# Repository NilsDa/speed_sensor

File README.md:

# Speed_Sensor

This Repository contains the complete KiCad project of the speed_sensor PCB design as well as important Datasheets and lots of random files and data relating to the project.

## important directories

- **/Datasheets** -> self explanatory
- **/KiCad** -> complete KiCad project and resulting gerber files for pcb printing.
- /Software -> miscellaneous software created mainly to experiment with certain things. not critical
- rest: unsorted files and folders containing parts-lists/footprints/... (need to be properly sorted)

## possibilities for simplifying the design

- maybe ditch the rechargeable lithium battery and use a small coin battery (CR2032) instead... majorly simplifies the PCB design and reduces friction points... But, rechargeable would be nice... Just something to think about.

## LICENSE

No license because project is properly unfinished :D Whoever would want access, needs to contact me.

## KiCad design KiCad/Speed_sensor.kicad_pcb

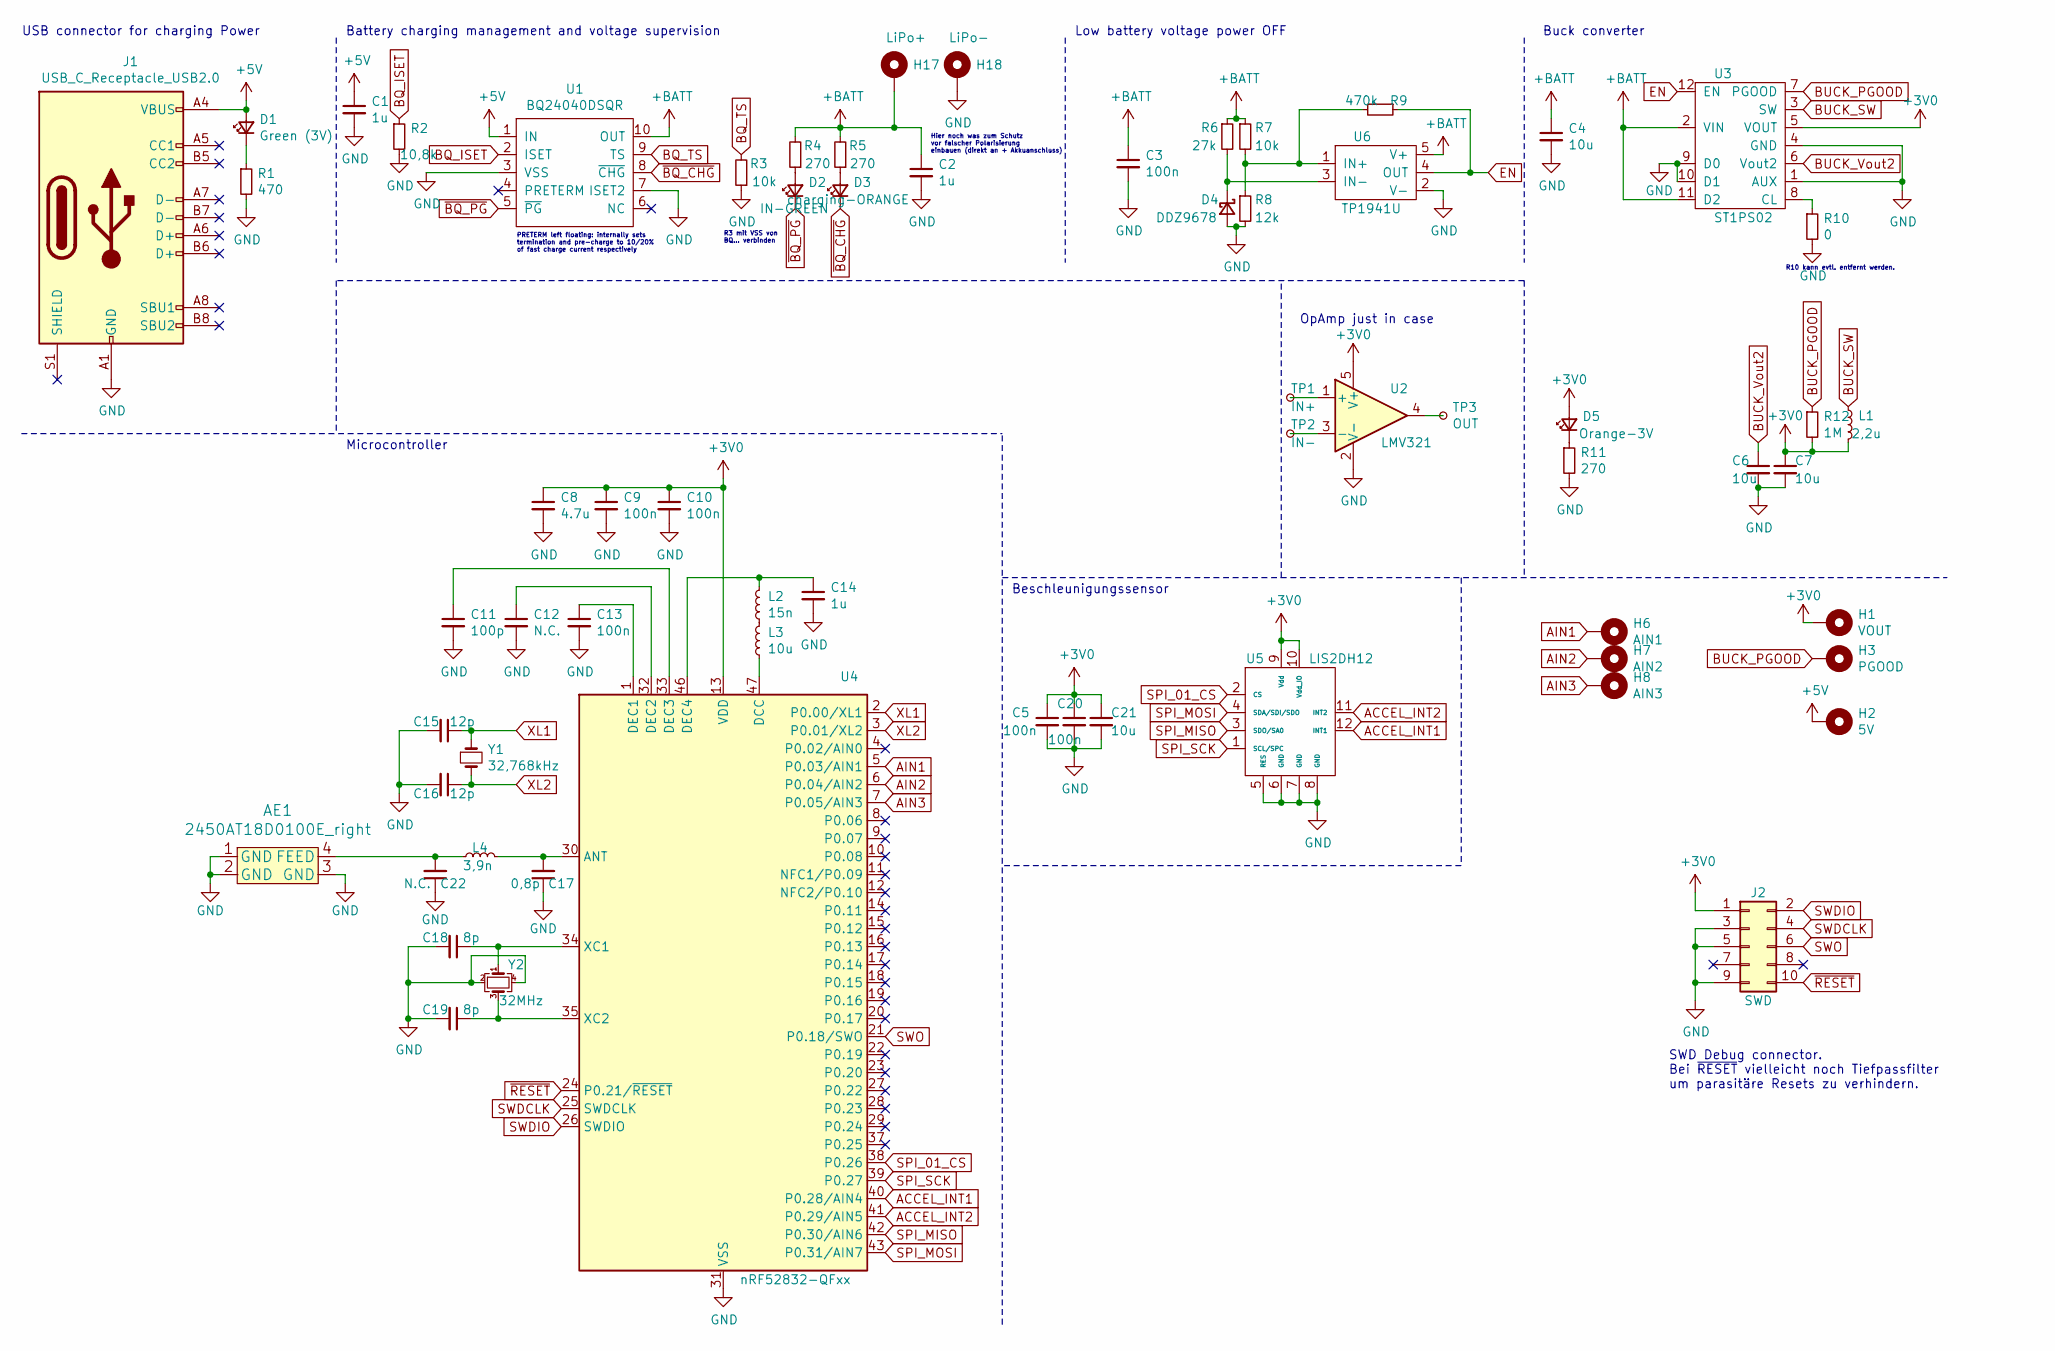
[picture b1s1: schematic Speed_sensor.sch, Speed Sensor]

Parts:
AE1: 2450AT18D0100E_right; 2450AT18D0100E
C1, C2, C14: 1u; C_0603_1608Metric_Pad1.08x0.95mm_HandSolder
C3, C5, C9, C10, C13, C20: 100n; C_0402_1005Metric_Pad0.74x0.62mm_HandSolder
C4, C6, C7, C21: 10u; C_0603_1608Metric_Pad1.08x0.95mm_HandSolder
C8: 4.7u; C_0603_1608Metric_Pad1.08x0.95mm_HandSolder
C11: 100p; C_0402_1005Metric_Pad0.74x0.62mm_HandSolder
C12, C22: N.C.; C_0402_1005Metric_Pad0.74x0.62mm_HandSolder
C15, C16: 12p; C_0402_1005Metric_Pad0.74x0.62mm_HandSolder
C17: 0,8p; C_0402_1005Metric_Pad0.74x0.62mm_HandSolder
C18, C19: 8p; C_0402_1005Metric_Pad0.74x0.62mm_HandSolder
D1: Green (3V); D_0603_1608Metric_Pad1.05x0.95mm_HandSolder
D2: IN-GREEN; D_0603_1608Metric_Pad1.05x0.95mm_HandSolder
D3: charging-ORANGE; D_0603_1608Metric_Pad1.05x0.95mm_HandSolder
D4: DDZ9678; D_SOD-123
D5: Orange-3V; D_0603_1608Metric_Pad1.05x0.95mm_HandSolder
H1: VOUT; TestPoint_Pad_D1.5mm
H2: 5V; TestPoint_Pad_D1.5mm
H3: PGOOD; TestPoint_Pad_D1.5mm
H6: AIN1; TestPoint_Pad_D1.5mm
H7: AIN2; TestPoint_Pad_D1.5mm
H8: AIN3; TestPoint_Pad_D1.5mm
H17: LiPo+; TestPoint_Plated_Hole_D2.0mm
H18: LiPo-; TestPoint_Plated_Hole_D2.0mm
J1: USB_C_Receptacle_USB2.0; USB_C_Receptacle_Palconn_UTC16-G_breitePins
J2: SWD; PinHeader_2x05_P1.27mm_Vertical_SMD
L1: 2,2u; L_0805_2012Metric_Pad1.15x1.40mm_HandSolder
L2: 15n; L_0402_1005Metric_Pad0.77x0.64mm_HandSolder
L3: 10u; L_0603_1608Metric_Pad1.05x0.95mm_HandSolder
L4: 3,9n; L_0402_1005Metric_Pad0.77x0.64mm_HandSolder
R1: 470; R_0402_1005Metric_Pad0.72x0.64mm_HandSolder
R2: 10,8k; R_0603_1608Metric_Pad0.98x0.95mm_HandSolder
R3: 10k; R_0603_1608Metric_Pad0.98x0.95mm_HandSolder
R4, R5, R11: 270; R_0402_1005Metric_Pad0.72x0.64mm_HandSolder
R6: 27k; R_0402_1005Metric_Pad0.72x0.64mm_HandSolder
R7: 10k; R_0402_1005Metric_Pad0.72x0.64mm_HandSolder
R8: 12k; R_0402_1005Metric_Pad0.72x0.64mm_HandSolder
R9: 470k; R_0402_1005Metric_Pad0.72x0.64mm_HandSolder
R10: 0; R_0402_1005Metric_Pad0.72x0.64mm_HandSolder
R12: 1M; R_0402_1005Metric_Pad0.72x0.64mm_HandSolder
TP1: IN+; TestPoint_Pad_D1.5mm
TP2: IN-; TestPoint_Pad_D1.5mm
TP3: OUT; TestPoint_Pad_D1.5mm
U1: BQ24040DSQR; BQ24040DSQR_breitePins
U2: LMV321; SOT-23-5_HandSoldering
U3: ST1PS02; ST1PS02CQTR_breitePins
U4: nRF52832-QFxx; QFN-48-1EP_6x6mm_P0.4mm_EP4.6x4.6mm_Handsolder
U5: LIS2DH12; LGA-12_2x2mm_P0.5mm_Handsolder
U6: TP1941U; SOT-353_SC-70-5_Handsoldering
Y1: 32,768kHz; Crystal_SMD_G8-2Pin_3.2x1.5mm
Y2: 32MHz; SMD-2016_4P

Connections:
+3V0: C5.1, C7.1, C8.1, C9.1, C10.1, C20.1, C21.1, D5.2 (A), H1.1, J2.1, L1.2, R12.2, U2.5 (V+), U3.5 (VOUT), U4.13 (VDD), U4.36 (VDD), U4.48 (VDD), U5.9 (Vdd), U5.10 (Vdd_IO)
+5V: C1.1, D1.2 (A), H2.1, J1.A4 (VBUS), J1.A9 (VBUS), J1.B4 (VBUS), J1.B9 (VBUS), U1.1 (IN); also elsewhere on the board
+BATT: C2.1, C3.1, C4.1, H17.1, R4.2, R5.2, R6.1, R7.1, U1.10 (OUT), U3.2 (VIN), U3.11 (D2), U6.5 (V+)
ACCEL_INT1: U4.40 (P0.28/AIN4), U5.12 (INT1)
ACCEL_INT2: U4.41 (P0.29/AIN5), U5.11 (INT2)
AIN1: H6.1, U4.5 (P0.03/AIN1)
AIN2: H7.1, U4.6 (P0.04/AIN2)
AIN3: H8.1, U4.7 (P0.05/AIN3)
BQ_ISET: R2.1, U1.2 (ISET)
BQ_TS: R3.2, U1.9 (TS)
BUCK_PGOOD: H3.1, R12.1, U3.7 (PGOOD)
BUCK_SW: L1.1, U3.3 (SW)
BUCK_Vout2: C6.1, U3.6 (Vout2)
EN: R9.1, U3.12 (EN), U6.4 (OUT)
GND: AE1.1 (GND), AE1.2 (GND), AE1.3 (GND), C1.2, C2.2, C3.2, C4.2, C5.2, C6.2, C7.2, C8.2, C9.2, C10.2, C11.2, C12.2, C13.2, C14.2, C15.2, C16.2, C17.1, C18.2, C19.2, C20.2, C21.2, C22.1, D4.2 (A), H18.1, J1.A1 (GND), J1.A12 (GND), J1.B1 (GND), J1.B12 (GND), J2.3, J2.5, J2.9, R1.2, R2.2, R3.1, R8.2, R10.2, R11.2, U1.3 (VSS), U1.7 (ISET2), U2.2 (V-), U3.1 (AUX), U3.4 (GND), U3.9 (D0), U3.10 (D1), U4.31 (VSS), U4.45 (VSS), U4.49 (VSS), U5.5 (RES), U5.6 (GND), U5.7 (GND), U5.8 (GND), U6.2 (V-), Y2.2, Y2.4
unnamed: AE1.4 (FEED), C22.2, L4.1
unnamed: C11.1, U4.33 (DEC3)
unnamed: C12.1, U4.32 (DEC2)
unnamed: C13.1, U4.1 (DEC1)
unnamed: C14.1, L2.2, U4.46 (DEC4)
unnamed: C17.2, L4.2, U4.30 (ANT)
unnamed: C18.1, U4.34 (XC1), Y2.1
unnamed: C19.1, U4.35 (XC2), Y2.3
unnamed: D1.1 (K), R1.1
unnamed: D2.2 (A), R4.1
unnamed: D3.2 (A), R5.1
unnamed: D4.1 (K), R6.2, U6.3 (IN-)
unnamed: D5.1 (K), R11.1
unnamed: L2.1, L3.2
unnamed: L3.1, U4.47 (DCC)
unnamed: R7.2, R8.1, R9.2, U6.1 (IN+)
unnamed: R10.1, U3.8 (CL)
unnamed: TP1.1, U2.1 (+)
unnamed: TP2.1, U2.3 (-)
unnamed: TP3.1, U2.4
SPI_01_CS: U4.38 (P0.26), U5.2 (CS)
SPI_MISO: U4.42 (P0.30/AIN6), U5.3 (SDO/SA0)
SPI_MOSI: U4.43 (P0.31/AIN7), U5.4 (SDA/SDI/SDO)
SPI_SCK: U4.39 (P0.27), U5.1 (SCL/SPC)
SWDCLK: J2.4, U4.25 (SWDCLK)
SWDIO: J2.2, U4.26 (SWDIO)
SWO: J2.6, U4.21 (P0.18/SWO)
XL1: C15.1, U4.2 (P0.00/XL1), Y1.1
XL2: C16.1, U4.3 (P0.01/XL2), Y1.2
~BQ_CHG~: D3.1 (K), U1.8 (~CHG~)
~BQ_PG~: D2.1 (K), U1.5 (~PG~)
~RESET~: J2.10, U4.24 (P0.21/~RESET)

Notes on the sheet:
Microcontroller
Beschleunigungssensor
SWD Debug connector. Bei ~RESET~ vielleicht noch Tiefpassfilter um parasitäre Resets zu verhindern.
USB connector for charging Power
Battery charging management and voltage supervision
Hier noch was zum Schutz vor falscher Polarisierung einbauen (direkt an + Akkuanschluss)
Low battery voltage power OFF
Buck converter
PRETERM left floating: internally sets termination and pre-charge to 10/20% of fast charge current respectively
R10 kann evtl. entfernt werden.
R3 mit VSS von BQ... verbinden
OpAmp just in case

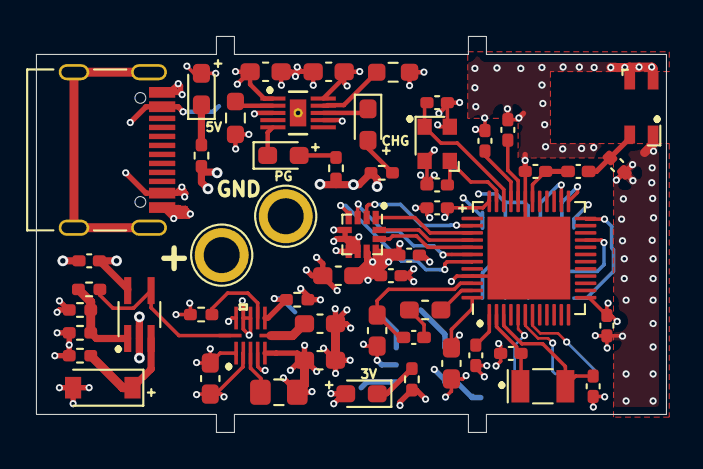
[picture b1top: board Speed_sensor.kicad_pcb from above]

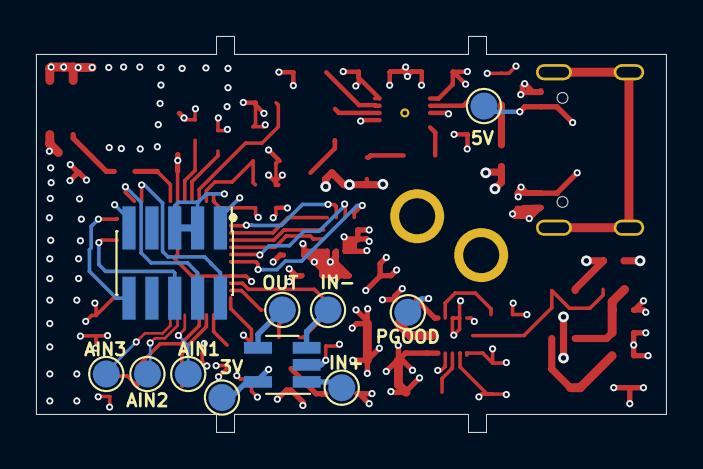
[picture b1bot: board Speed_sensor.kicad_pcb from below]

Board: 4 copper layers, 35.0 x 22.0 mm, 65 parts (11 on the bottom side), 47 nets.

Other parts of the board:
5V: 5V; TestPoint_Pad_D1.5mm

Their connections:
+5V: 5V.1; also elsewhere on the board

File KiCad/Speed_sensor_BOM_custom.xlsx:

Source: | C:\Users\nils_\OneDrive\Documents\Projekte\Speed_sensor\speed_sensor\KiCad\Spee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
Date: | 44328.924131944441
Tool: | Eeschema (5.1.9)-1
Component Count: | 61
Ref | Value | Footprint | Bestückung | Datasheet | Comment | LCSC part no. | hat Manu
AE1 | 2450AT18D0100E_right | myparts:2450AT18D0100E |  | ~ |  |  | ja
C1 | 1u | Capacitor_SMD:C_0603_1608Metric_Pad1.08x0.95mm_HandSolder | 16 | ~ |  | C1592 | nein
C2 | 1u | Capacitor_SMD:C_0603_1608Metric_Pad1.08x0.95mm_HandSolder | 16 | ~ |  | C1592 | nein
C3 | 100n | Capacitor_SMD:C_0402_1005Metric_Pad0.74x0.62mm_HandSolder | 2 | ~ |  | C392963 | ja, aber trotzdem bestellen
C4 | 10u | Capacitor_SMD:C_0603_1608Metric_Pad1.08x0.95mm_HandSolder | 17 | ~ |  | C319196 | nein
C5 | 100n | Capacitor_SMD:C_0402_1005Metric_Pad0.74x0.62mm_HandSolder | 2 | ~ |  | C392963 | ja, aber trotzdem bestellen
C6 | 10u | Capacitor_SMD:C_0603_1608Metric_Pad1.08x0.95mm_HandSolder | 17 | ~ |  | C319196 | nein
C7 | 10u | Capacitor_SMD:C_0603_1608Metric_Pad1.08x0.95mm_HandSolder | 17 | ~ |  | C319196 | nein
C8 | 4.7u | Capacitor_SMD:C_0603_1608Metric_Pad1.08x0.95mm_HandSolder | 18 | ~ |  | C19666 | nein
C9 | 100n | Capacitor_SMD:C_0402_1005Metric_Pad0.74x0.62mm_HandSolder | 2 | ~ |  | C392963 | ja, aber trotzdem bestellen
C10 | 100n | Capacitor_SMD:C_0402_1005Metric_Pad0.74x0.62mm_HandSolder | 2 | ~ |  | C392963 | ja, aber trotzdem bestellen
C11 | 100p | Capacitor_SMD:C_0402_1005Metric_Pad0.74x0.62mm_HandSolder | 3 | ~ |  | C696853 | ja
C12 | N.C. | Capacitor_SMD:C_0402_1005Metric_Pad0.74x0.62mm_HandSolder |  | ~ |  |  | -
C13 | 100n | Capacitor_SMD:C_0402_1005Metric_Pad0.74x0.62mm_HandSolder | 2 | ~ |  | C392963 | ja, aber trotzdem bestellen
C14 | 1u | Capacitor_SMD:C_0603_1608Metric_Pad1.08x0.95mm_HandSolder | 16 | ~ |  | C1592 | nein
C15 | 12p | Capacitor_SMD:C_0402_1005Metric_Pad0.74x0.62mm_HandSolder | 1 | ~ |  | C26406 | nein
C16 | 12p | Capacitor_SMD:C_0402_1005Metric_Pad0.74x0.62mm_HandSolder | 1 | ~ |  | C26406 | nein
C17 | 0,8p | Capacitor_SMD:C_0402_1005Metric_Pad0.74x0.62mm_HandSolder | 4 | ~ |  | C40459 | ja
C18 | 8p | Capacitor_SMD:C_0402_1005Metric_Pad0.74x0.62mm_HandSolder | 5 | ~ |  | C258500 | nein
C19 | 8p | Capacitor_SMD:C_0402_1005Metric_Pad0.74x0.62mm_HandSolder | 5 | ~ |  | C258500 | nein
C20 | 100n | Capacitor_SMD:C_0402_1005Metric_Pad0.74x0.62mm_HandSolder | 2 | ~ |  | C392963 | ja, aber trotzdem bestellen
C21 | 10u | Capacitor_SMD:C_0603_1608Metric_Pad1.08x0.95mm_HandSolder | 17 | ~ |  | C319196 | nein
C22 | N.C. | Capacitor_SMD:C_0402_1005Metric_Pad0.74x0.62mm_HandSolder |  | ~ |  |  | -
D1 | Green (3V) | Diode_SMD:D_0603_1608Metric_Pad1.05x0.95mm_HandSolder |  | ~ |  | C205443 | ja
D2 | IN-GREEN | Diode_SMD:D_0603_1608Metric_Pad1.05x0.95mm_HandSolder |  | ~ |  | C205443 | ja
D3 | charging-ORANGE | Diode_SMD:D_0603_1608Metric_Pad1.05x0.95mm_HandSolder |  | ~ |  | C205445 | ja
D4 | DDZ9678 | Diode_SMD:D_SOD-123 |  | ~ |  | C150464 | ja
D5 | Orange-3V | Diode_SMD:D_0603_1608Metric_Pad1.05x0.95mm_HandSolder |  | ~ |  | C205445 | ja
H1 | VOUT | TestPoint:TestPoint_Pad_D1.5mm |  | ~ |  |  | -
H3 | PGOOD | TestPoint:TestPoint_Pad_D1.5mm |  | ~ |  |  | -
H6 | AIN1 | TestPoint:TestPoint_Pad_D1.5mm |  | ~ |  |  | -
H7 | AIN2 | TestPoint:TestPoint_Pad_D1.5mm |  | ~ |  |  | -
H8 | AIN3 | TestPoint:TestPoint_Pad_D1.5mm |  | ~ |  |  | -
H17 | LiPo+ | TestPoint:TestPoint_Plated_Hole_D2.0mm |  | ~ |  |  | -
H18 | LiPo- | TestPoint:TestPoint_Plated_Hole_D2.0mm |  | ~ |  |  | -
J1 | USB_C_Receptacle_USB2.0 | myparts:USB_C_Receptacle_Palconn_UTC16-G_breitePins |  | https://www.usb.org/sites/default/files/documents/usb_type-c.zip |  | C165948 | nein
J2 | SWD | Connector_PinHeader_1.27mm:PinHeader_2x05_P1.27mm_Vertical_SMD |  | ~
L1 | 2,2u | Inductor_SMD:L_0805_2012Metric_Pad1.15x1.40mm_HandSolder | 22 | ~ |  | C95973 | nein
L2 | 15n | Inductor_SMD:L_0402_1005Metric_Pad0.77x0.64mm_HandSolder | 6 | ~ |  | C329619 | nein
L3 | 10u | Inductor_SMD:L_0603_1608Metric_Pad1.05x0.95mm_HandSolder | 19 | ~ |  | C1035 | nein
L4 | 3,9n | Inductor_SMD:L_0402_1005Metric_Pad0.77x0.64mm_HandSolder | 7 | ~ |  | C90196 | ja
R1 | 470 | Resistor_SMD:R_0402_1005Metric_Pad0.72x0.64mm_HandSolder | 8 | ~ | verwende 510 | C25170 | ja
R2 | 10,8k | Resistor_SMD:R_0603_1608Metric_Pad0.98x0.95mm_HandSolder | 20 | ~ | verwende 10,7k | C22857 | nein
R3 | 10k | Resistor_SMD:R_0603_1608Metric_Pad0.98x0.95mm_HandSolder | 21 | ~ |  | C305012 | ja (nur 20)
R4 | 270 | Resistor_SMD:R_0402_1005Metric_Pad0.72x0.64mm_HandSolder | 9 | ~ |  | C310256 | ja
R5 | 270 | Resistor_SMD:R_0402_1005Metric_Pad0.72x0.64mm_HandSolder | 9 | ~ |  | C310256 | ja
R6 | 27k | Resistor_SMD:R_0402_1005Metric_Pad0.72x0.64mm_HandSolder | 10 | ~ |  | C304599 | ja
R7 | 10k | Resistor_SMD:R_0402_1005Metric_Pad0.72x0.64mm_HandSolder | 11 | ~ |  | C140214 | ja
R8 | 12k | Resistor_SMD:R_0402_1005Metric_Pad0.72x0.64mm_HandSolder | 12 | ~ |  | C25535 | ja
R9 | 470k | Resistor_SMD:R_0402_1005Metric_Pad0.72x0.64mm_HandSolder | 13 | ~ |  | C294637 | ja
R10 | 0 | Resistor_SMD:R_0402_1005Metric_Pad0.72x0.64mm_HandSolder | 14 | ~ |  | C60485 | ja
R11 | 270 | Resistor_SMD:R_0402_1005Metric_Pad0.72x0.64mm_HandSolder | 9 | ~ |  | C310256 | ja
R12 | 1M | Resistor_SMD:R_0402_1005Metric_Pad0.72x0.64mm_HandSolder | 15 | ~ |  | C26087 | ja
U1 | BQ24040DSQR | Package_WSON-10:BQ24040DSQR_breitePins |  |  |  | C81080 | ja
U2 | LMV321 | Package_TO_SOT_SMD:SOT-23-5_HandSoldering |  | http://www.ti.com/lit/ds/symlink/lmv324.pdf |  |  | ja
U3 | ST1PS02 | Package_TQFN-12:ST1PS02CQTR_breitePins |  |  | Free Sample (5x) |  | nein
U4 | nRF52832-QFxx | myparts:QFN-48-1EP_6x6mm_P0.4mm_EP4.6x4.6mm_Handsolder |  | http://infocenter.nordicsemi.com/pdf/nRF52832_PS_v1.4.pdf |  |  | ja
U5 | LIS2DH12 | myparts:LGA-12_2x2mm_P0.5mm_Handsolder |  |  |  | C110926 | ja
U6 | TP1941U | Package_TO_SOT_SMD:SOT-353_SC-70-5_Handsoldering |  |  |  | C248711 | ja
Y1 | 32,768kHz | Crystal:Crystal_SMD_G8-2Pin_3.2x1.5mm |  | ~ |  |  | ja
Y2 | 32MHz | myparts:SMD-2016_4P |  | ~ |  |  | ja

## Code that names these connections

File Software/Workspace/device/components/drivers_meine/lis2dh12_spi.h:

/*

Driver for lis2dh12 connected via SPI

Autor: Nils Daub

this driver is specific to the 
*/

#ifndef LIS2DH12_SPI_H
#define LIS2DH12_SPI_H

#ifdef __cplusplus
extern "C" {
#endif

// includes
// #include "lis2dh12_internal.h"
#include "nrf_drv_spi.h"
#include "nrf_gpio.h"


/**
 * @brief Possible sensor addresses.
 */
#define LIS2DH12_BASE_ADDRESS_LOW       0x18U
#define LIS2DH12_BASE_ADDRESS_HIGH      0x19U

// WHO_AM_I default value.
#define LIS2DH12_REG_WHO_AM_I_DEFAULT_VALUE 0x33

// lis2dh12 registers
#define LIS2DH12_REG_STATUS_AUX         0x07
#define LIS2DH12_REG_OUT_TEMP_L         0x0C
#define LIS2DH12_REG_OUT_TEMP_H         0x0D
#define LIS2DH12_REG_WHO_AM_I           0x0F
#define LIS2DH12_REG_CTRL_REG0          0x1E
#define LIS2DH12_REG_TEMP_CFG_REG       0x1F
#define LIS2DH12_REG_CTRL_REG1          0x20
#define LIS2DH12_REG_CTRL_REG2          0x21
#define LIS2DH12_REG_CTRL_REG3          0x22
#define LIS2DH12_REG_CTRL_REG4          0x23
#define LIS2DH12_REG_CTRL_REG5          0x24
#define LIS2DH12_REG_CTRL_REG6          0x25
#define LIS2DH12_REG_REFERENCE          0x26
#define LIS2DH12_REG_STATUS             0x27
#define LIS2DH12_REG_OUT_X_L            0x28
#define LIS2DH12_REG_OUT_X_H            0x29
#define LIS2DH12_REG_OUT_Y_L            0x2A
#define LIS2DH12_REG_OUT_Y_H            0x2B
#define LIS2DH12_REG_OUT_Z_L            0x2C
#define LIS2DH12_REG_OUT_Z_H            0x2D
#define LIS2DH12_REG_FIFO_CTRL          0x2E
#define LIS2DH12_REG_FIFO_SRC           0x2F
#define LIS2DH12_REG_INT1_CFG           0x30
#define LIS2DH12_REG_INT1_SRC           0x31
#define LIS2DH12_REG_INT1_THS           0x32
#define LIS2DH12_REG_INT1_DURATION      0x33
#define LIS2DH12_REG_INT2_CFG           0x34
#define LIS2DH12_REG_INT2_SRC           0x35
#define LIS2DH12_REG_INT2_THS           0x36
#define LIS2DH12_REG_INT2_DURATION      0x37
#define LIS2DH12_REG_CLICK_CFG          0x38
#define LIS2DH12_REG_CLICK_SRC          0x39
#define LIS2DH12_REG_CLICK_THS          0x3A
#define LIS2DH12_REG_TIME_LIMIT         0x3B
#define LIS2DH12_REG_TIME_LATENCY       0x3C
#define LIS2DH12_REG_TIME_WINDOW        0x3D
#define LIS2DH12_REG_ACT_THS            0x3E
#define LIS2DH12_REG_ACT_DUR            0x3F


// SPI buffer
#define SPI_BUFSIZE 8   // 8 byte SPI buffer size
static uint8_t spi_tx_buf[SPI_BUFSIZE];    // transfer buffer
static uint8_t spi_rx_buf[SPI_BUFSIZE];    // receive buffer


// set read or write operation
#define SET_READ_SINGLE_CMD(x) (x | 0x80)   // set MSB to 1 for read operation



static volatile bool spi_xfer_done;     // transmission completion flag



/*
Event Handler
setting flag spi_xfer_done (to indicate communication has completed)
*/
void spi_event_handler(nrf_drv_spi_evt_t const * p_event, void * p_context);


/*
init function for spi connection to this sensor
input: spi instance
*/
//void LIS2DH12_spi_init(nrf_drv_spi_t const * const spi_instance, int LIS2DH12_SS_PIN, int SPI_MISO_PIN, int SPI_MOSI_PIN, int SPI_SCK_PIN);
void LIS2DH12_spi_init(nrf_drv_spi_t const * const spi_instance, nrf_drv_spi_config_t spi_config);


/*
function to read specified Register
*/
int LIS2DH12_read_reg(nrf_drv_spi_t const * const spi_instance, int reg);

/*
function to write a Byte into specified register
*/
void LIS2DH12_write_reg(nrf_drv_spi_t const * const spi_instance, int reg, int write_reg);

/*
function to enable Power-down mode (current consumption 0,5uA)
*/
void LIS2DH12_power_down_mode(nrf_drv_spi_t const * const spi_instance);

/*
function to disable power-down/enable low-power mode (25Hz; 6uA)
*/
void LIS2DH12_low_power_mode(nrf_drv_spi_t const * const spi_instance);


#ifdef __cplusplus
}
#endif

#endif // LIS2DH12_SPI_H

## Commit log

2021-04-26 some datasheets
2021-04-26 all initial KiCad files (only schematics started)
2021-04-26 added cd of this folder to not waste time
2021-04-26 hierarchische Aufteilung der Schematic angefangen & power circuit um Battery management + usb connector erweitert
2021-04-26 Schematic ein bisschen sortiert
2021-04-26 added green LED for when USB is connected to power circuit
2021-04-26 changed SPI labels to make it more general and not specific to the BMA Sensor
2021-04-26 added battery voltage supervision version 1
2021-04-26 added files for reference design for cc2570
2021-04-27 corrected battery voltage supervision
2021-04-27 paar Kommentare/Ideen zur voltage supervision hinzugefügt
2021-04-27 int pins am BMA hinzugefügt (aber noch nicht an nrf angeschlossen
2021-04-27 ANT bauteile vom nrf entfernt
2021-04-27 Kommentar zum ANT Modul
2021-04-27 kleines Kommentar angepasst
2021-04-27 paar Sachen mit Manu angepasst
2021-04-27 power circuit übersichtlicher gemacht, low battery voltage detection verändert.
2021-04-28 updated battery charging with Manus chip, added low frequency crystal
2021-04-28 switch to Manus Accelerometer, switch back to A4 page size
2021-04-28 buck converter circuit made more readable
2021-04-28 antenna added
2021-04-28 added pads for all AINx, decided on which GPIO to use (wil prop change again)
2021-04-28 added small comment)
2021-04-28 added all annotations
2021-04-28 added a lot of footprints (mainly crystal and all the chips are missing)
2021-04-30 added all footprints (LFO crystal might have to be updated)
2021-04-30 custom footprints von Manu übernommen (jetzt sollte alles passen), PCB layout angefangen.
2021-04-30 layout update (Bauteile um den nrf grob positioniert)
2021-04-30 parts of power circuit roughly layouted
2021-04-30 parts of power circuit roughly layouted, again
2021-04-30 layout. parts roughly put into the right spot
2021-05-01 played around with part positioning slightly
2021-05-01 small changes in the layout
2021-05-02 layout part placement (again, very small changes)
2021-05-02 changed some labels in the .sch so all power stuff is labeled correctly
2021-05-02 changed which GPIO pins are used for SPI
2021-05-04 layout part positions changed slightly, added 3,5cm x 2cm outline (as a goal)
2021-05-04 defined PCB size 35mm x 20mm, started rearranging layout (starting with power circuit (5V + Batt low voltage turn OFF)
2021-05-04 added Buck converter part to the properly sized layout
2021-05-04 Bauteilbezeichnungen auf nicht mehr sichtbar gemacht
2021-05-04 Layout um den nrf an Referenzlayout orientiert.
2021-05-04 kompletter power circuit kompakt im layout untergebracht.
2021-05-04 Bauteilplatzierungen leicht angepasst. Bemerkt, dass PCB wahrsch größer werden muss.
2021-05-05 kleine Änderungen an Bauteilplatzierungen um vias unterbringen zu können, 'keepout area' für Antenne eingefügt.
2021-05-05 Änderungen nach Treffen mit Manu, opamp für alle Fälle, opamp footprint geändert, C footprint in impedance matching circuit hinzugefügt, SWD connector footprint geändert.
2021-05-05 upgrade auf USB-C connector & footprint
2021-05-05 buck converter footprint pads verkleinert, nrf + naheliegende bauteile gedreht eingefügt, Antenne neu platziert
2021-05-08 Datasheet für quarz hinzugefügt, kleine änderungen am Layout (nichts nennenswertes)
2021-05-10 power und GND plane aufgeteilt (quarze noch nicht beachtet, Antenne aber schon)
2021-05-10 angefangen mit dem routing
2021-05-10 erste Layout-version fast fertig geroutet
2021-05-10 nochmal bisschen am Layout
2021-05-10 Änderungen am layout: vias, leitungen & pads leicht umplatziert
2021-05-10 kleine layout-änderungen, mal wieder
2021-05-12 angefangen die genauen Bauteile zuzuordnen, paar footprints geändert (LED-widerstände von 0603 zu 0402)
2021-05-12 weitere Bauteile zugeordnet (Widerstände und Dioden)
2021-05-15 unbedeutende kleine Änderungen am Layout.
2021-05-19 updated footprint L1, BOM erweitert und weitere Teile zugeordnet
2021-05-20 im layout paar Bezeichnungen entfernt (die zurück gekommen sind nachdem footprints geändert wurden)
2021-05-21 erste Beschriftungen ins Layout eingefügt (sehr wenig, rückseite kann noch nichts eingefügt werden...)
2021-05-22 paar Markierungen für + Voltage sowie PIN1 im layout hinzugefügt
2021-05-29 restliche Bauteile zugeornet und raus gesucht (bei LCSC bereit zum Bestellen); restliche Markierungen im Layout gemacht; 4 Kerben an langen Seiten des PCB hinzugefügt um ggf. PCB in Gehäuse zu drücke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
2021-05-29 erste Bestellung bei LCSC gemacht (siehe excel-tabelle)
2021-05-29 design rule check im layout durchgeführt und kleinigkeiten angepasst
2021-05-29 alle Files zum Bestellen erstellt und Bestellungen bei jlcpcb und lcsc raus geschickt :).
2021-05-31 segger embeded Studio installiert und erstes Projekt erstellt.
2021-06-05 unnötige Dateien entfernt.
2021-06-05 visual studio code Workspace angelegt und relevante Teile des SDK eingefügt. erste CMakeLists erstellt und erste anpassungen gemacht.
2021-06-07 .gitignore hinzugefügt und SDK sowie ein paar andere Sachen hinzugefügt; SDK nochmal mit allen Ordnern (außer examples) hinzugefügt.
2021-06-07 build ordner zu .gitignore hinzugefügt.
2021-06-07 .xlsx der bestellung umbenannt (Monat berichtigt).
2021-06-07 source files in CMakeLists angepasst.
2021-06-07 linker file hinzugefügt
2021-06-09 paar Änderungen an der CMakeLists.txt von gestern; Excel der Bestellung vom 01.Juni angepasst (alles angekommen :)))
2021-06-18 CMakeLists.txt leicht angepasst
2021-07-19 BOM tabelle nach erster Bestückung
2021-07-21 some changes to CMakeLists; added some Matlab Test stuff
2021-07-21 connected BQ2404... Thermal Pad to GND
2021-07-21 added 5V Test Pad on backside
2021-07-21 added back-SilkS and all Pad-Names + Pin1 marking at SWD footprintgit status
2021-08-10 einfach GPIO Pin5 (AIN3) toggle Beispiel
2021-08-10 .../device/ Directory aus .gitignore entfernt
2021-08-10 .../device/ Directory hinzugefügt. (die ganze SDK eben)
2021-09-19 VScode zum funktionieren gebracht und LIS2DH12 driver angefangen
2021-09-20 submodule für Firmware hinzugefügt.
2021-09-20 kleine submodule tests
2021-09-20 get new submodule commits
2021-09-20 removing submodule
2021-09-20 removed vscode workspace file from .gitignore
2021-12-14 paar matlab files neu
